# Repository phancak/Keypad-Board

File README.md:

# STM32L010K4T6 Keypad Board  

## Overview  
This project features a **low-power, compact keypad module** based on the **STM32L010K4T6 MCU**, designed to function as a **mini keyboard** for embedded systems. The board includes **twelve tactile buttons**, with the STM32 MCU handling **debouncing and key scanning**, then transmitting keypress data to a host MCU via **I2C or UART**.  

This design optimizes processing efficiency on the host system by **offloading keypad management to the STM32L010K4T6**, making it ideal for applications requiring reliable **user input with minimal power consumption**.  

## Features  
✅ **STM32L010K4T6 MCU** – Ultra-low-power ARM Cortex-M0+ processor  
✅ **12-Button Keypad** – Efficient, responsive user input  
✅ **I2C & UART Communication** – Flexible interfacing with host MCUs  
✅ **Debouncing & Key Scanning** – Handled in firmware for accurate input detection  
✅ **Low Power Mode** – Automatic sleep mode when idle to conserve energy  

## Applications  
- **Embedded Systems** – User interface for microcontroller-based projects  
- **IoT Devices** – Low-power control panel for smart devices  
- **Industrial Automation** – Secure keypad entry for control units  

## Getting Started  
### Hardware Requirements  
- STM32L010K4T6 Keypad Board  
- Host MCU (STM32, ESP32, Raspberry Pi, etc.)  
- Power Supply (3.3V)  
- USB-to-Serial Debugging Tools  

### Software Requirements  
- **STM32CubeIDE** – Firmware development  
- **I2C/UART Libraries** – Communication with the host MCU  
- **ST-Link or J-Link** – Debugging and flashing tools  

## Setup & Usage  
1. **Power the Board** – Provide 3.3V supply to the MCU.  
2. **Connect to Host MCU** – Use I2C or UART for communication.  
3. **Flash Firmware** – Load key scanning and communication code.  
4. **Receive Key Data** – Host MCU processes key events for input handling.  

## Repository Structure  
/Firmware - STM32 firmware source code
/Core - Main application files
/Drivers - HAL and LL peripheral drivers
/Keypad - Debouncing and key scanning logic
/Utils - Utility functions and helper libraries

/Hardware - PCB schematics and design files
/Schematic - Circuit diagrams (PDF, KiCad, Altium, etc.)
/PCB - Board layout files (Gerber, BOM, assembly files)

/Docs - Technical documentation and references
/Getting_Started - Setup guides, connection diagrams
/Datasheets - Component datasheets
/Application_Notes - Project use cases and performance analysis

/Examples - Sample projects demonstrating board usage
/I2C_Host - Example of interfacing via I2C
/UART_Host - Example of interfacing via UART

/Tools - Development tools and scripts
/Flashing_Scripts - Python scripts for automated flashing
/Debug_Scripts - Debugging utilities for logging

## Future Enhancements  
- 🔹 **Configurable Key Mapping** – Customize key assignments via firmware  
- 🔹 **Multi-Press Support** – Enable simultaneous key detection  
- 🔹 **Low-Power Optimization** – Further reduce power consumption for battery-based applications  

## License  
This project is open-source under the **MIT License**.  

---

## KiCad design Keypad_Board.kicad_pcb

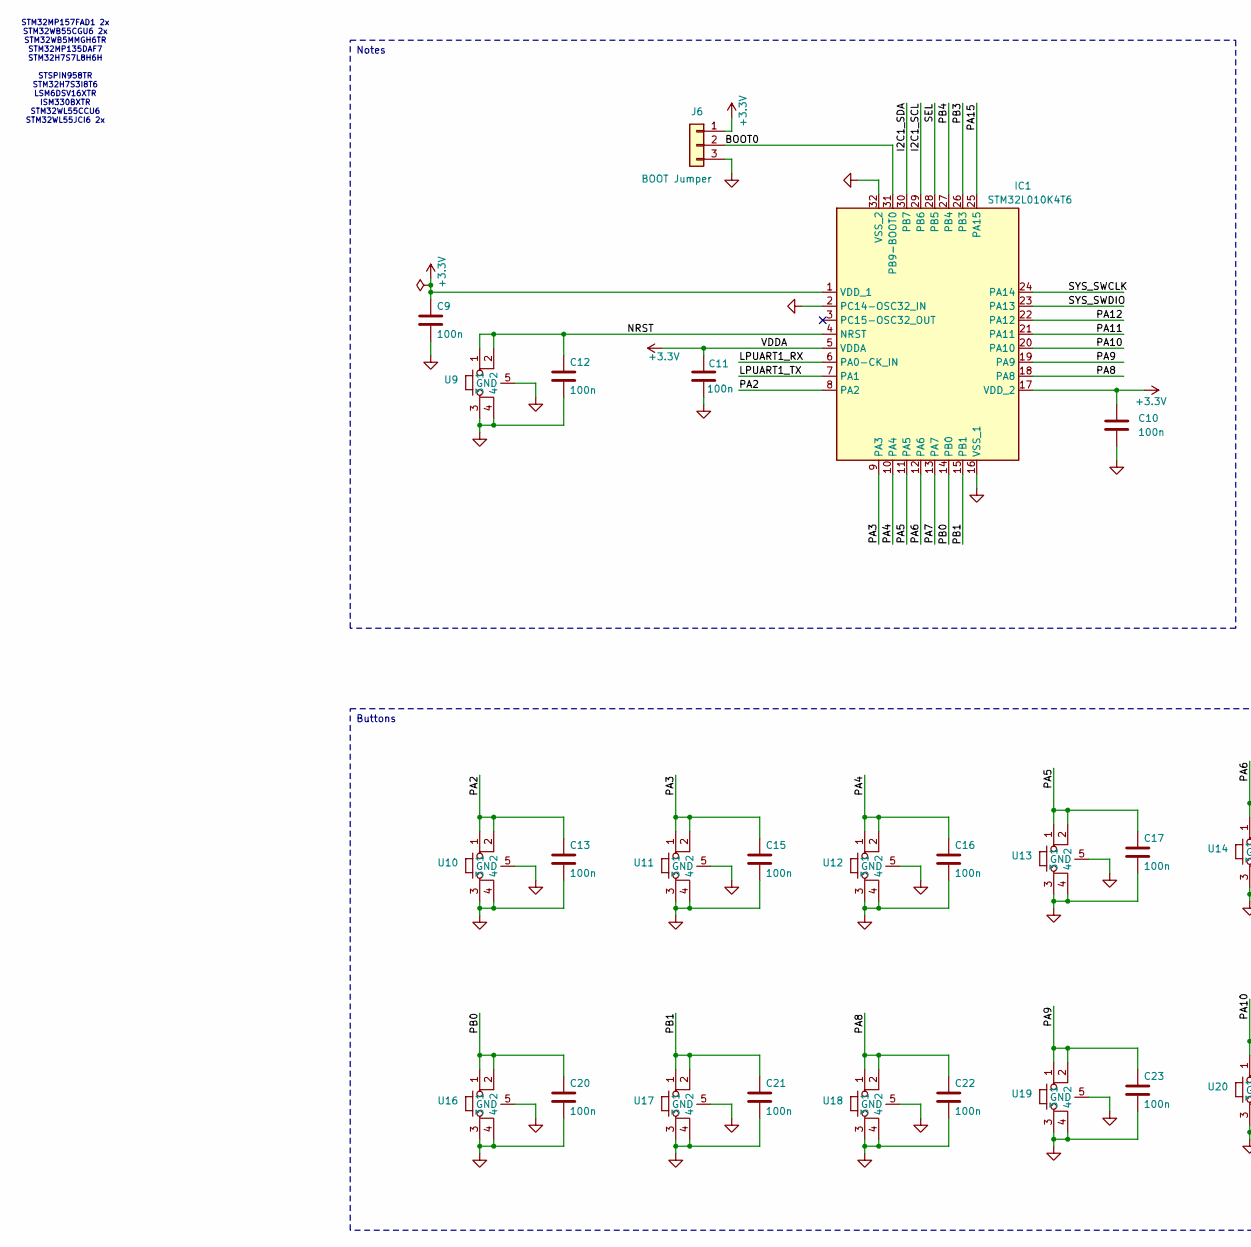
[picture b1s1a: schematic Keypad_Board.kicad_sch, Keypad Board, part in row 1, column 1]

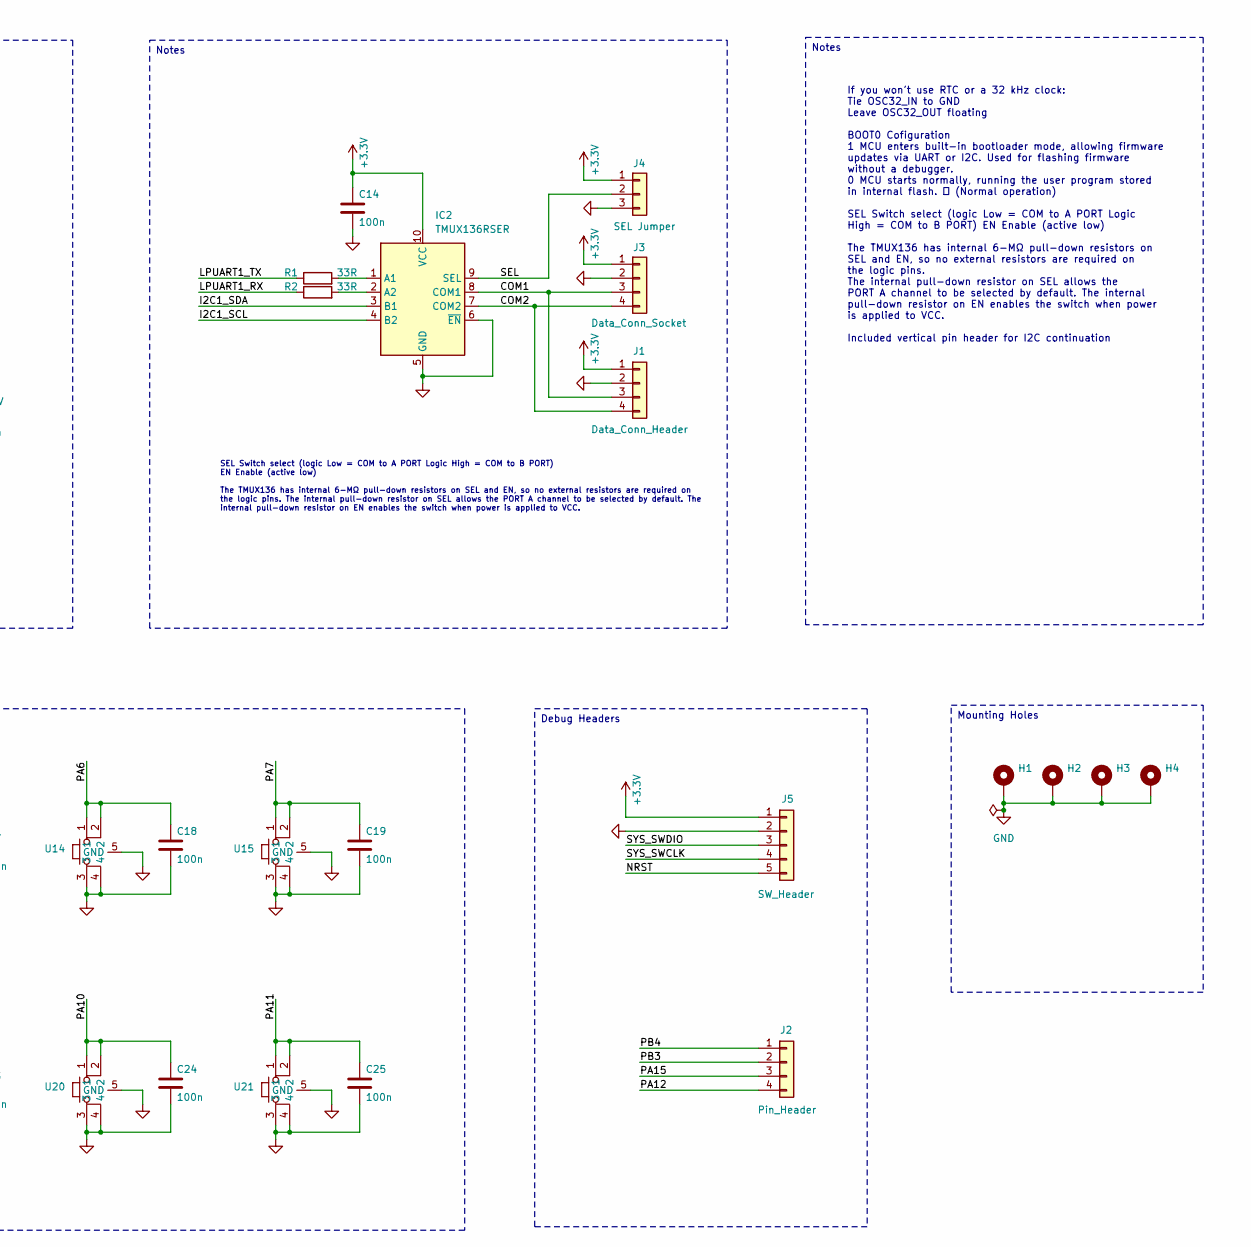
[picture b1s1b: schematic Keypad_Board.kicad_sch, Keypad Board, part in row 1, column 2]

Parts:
C9, C10, C11, C12, C13, C14, C15, C16, C17, C18, C19, C20, C21, C22, C23, C24, C25: 100n; C_0603_1608Metric_Pad1.08x0.95mm_HandSolder
H1, H2, H3, H4: MountingHole_Pad; MountingHole_3.2mm_M3_Pad
IC1: STM32L010K4T6; STM32L010K4T6 _QFP80P900X900X160-32N; Manufacturer_Part_Number STM32L010K4T6; Mouser Part Number 511-STM32L010K4T6
IC2: TMUX136RSER; Mouser Part Number 595-TMUX136RSER
J1: Data_Conn_Header; PinHeader_1x04_P2.54mm_Vertical
J2: Pin_Header; PinHeader_1x04_P2.54mm_Vertical
J3: Data_Conn_Socket; PinSocket_1x04_P2.54mm_Vertical
J4: SEL Jumper; PinHeader_1x03_P2.54mm_Vertical
J5: SW_Header; PinHeader_1x05_P2.54mm_Vertical
J6: BOOT Jumper; PinHeader_1x03_P2.54mm_Vertical
R1, R2: 33R; R_0805_2012Metric_Pad1.20x1.40mm_HandSolder
U9, U10, U11, U12, U13, U14, U15, U16, U17, U18, U19, U20, U21: Button_KMR231GLFS

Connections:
+3.3V: C9.1, C10.1, C11.1, C14.1, IC1.1 (VDD_1), IC1.5 (VDDA), IC1.17 (VDD_2), IC2.10 (VCC), J1.1, J3.1, J4.1, J5.1, J6.1
/BOOT0: IC1.31 (PB9-BOOT0), J6.2
/COM1: IC2.8 (COM1), J1.3, J3.3
/COM2: IC2.7 (COM2), J1.4, J3.4
/I2C1_SCL: IC1.29 (PB6), IC2.4 (B2)
/I2C1_SDA: IC1.30 (PB7), IC2.3 (B1)
/LPUART1_RX: IC1.6 (PA0-CK_IN), R2.1
/LPUART1_TX: IC1.7 (PA1), R1.1
/NRST: C12.1, IC1.4 (NRST), J5.5, U9.1, U9.2
/PA2: C13.1, IC1.8 (PA2), U10.1, U10.2
/PA3: C15.1, IC1.9 (PA3), U11.1, U11.2
/PA4: C16.1, IC1.10 (PA4), U12.1, U12.2
/PA5: C17.1, IC1.11 (PA5), U13.1, U13.2
/PA6: C18.1, IC1.12 (PA6), U14.1, U14.2
/PA7: C19.1, IC1.13 (PA7), U15.1, U15.2
/PA8: C22.1, IC1.18 (PA8), U18.1, U18.2
/PA9: C23.1, IC1.19 (PA9), U19.1, U19.2
/PA10: C24.1, IC1.20 (PA10), U20.1, U20.2
/PA11: C25.1, IC1.21 (PA11), U21.1, U21.2
/PA12: IC1.22 (PA12), J2.4
/PA15: IC1.25 (PA15), J2.3
/PB0: C20.1, IC1.14 (PB0), U16.1, U16.2
/PB1: C21.1, IC1.15 (PB1), U17.1, U17.2
/PB3: IC1.26 (PB3), J2.2
/PB4: IC1.27 (PB4), J2.1
/SEL: IC1.28 (PB5), IC2.9 (SEL), J4.2
/SYS_SWCLK: IC1.24 (PA14), J5.4
/SYS_SWDIO: IC1.23 (PA13), J5.3
GND: C9.2, C10.2, C11.2, C12.2, C13.2, C14.2, C15.2, C16.2, C17.2, C18.2, C19.2, C20.2, C21.2, C22.2, C23.2, C24.2, C25.2, H1.1, H2.1, H3.1, H4.1, IC1.2 (PC14-OSC32_IN), IC1.16 (VSS_1), IC1.32 (VSS_2), IC2.5 (GND), IC2.6 (~EN), J1.2, J3.2, J4.3, J5.2, J6.3, U9.3, U9.4, U9.5 (GND), U10.3, U10.4, U10.5 (GND), U11.3, U11.4, U11.5 (GND), U12.3, U12.4, U12.5 (GND), U13.3, U13.4, U13.5 (GND), U14.3, U14.4, U14.5 (GND), U15.3, U15.4, U15.5 (GND), U16.3, U16.4, U16.5 (GND), U17.3, U17.4, U17.5 (GND), U18.3, U18.4, U18.5 (GND), U19.3, U19.4, U19.5 (GND), U20.3, U20.4, U20.5 (GND), U21.3, U21.4, U21.5 (GND)
unnamed: IC2.1 (A1), R1.2
unnamed: IC2.2 (A2), R2.2

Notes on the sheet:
Notes
Debug Headers
Mounting Holes
Buttons
If you won't use RTC or a 32 kHz clock: Tie OSC32_IN to GND Leave OSC32_OUT floating BOOT0 Cofiguration 1 MCU enters built-in bootloader mode, allowing firmware updates via UART or I2C. Used for flashing firmware without a debugger. 0 MCU starts normally, running the user program stored in internal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
SEL Switch select (logic Low = COM to A PORT Logic High = COM to B PORT) EN Enable (active low) The TMUX136 has internal 6-MΩ pull-down resistors on SEL and EN, so no external resistors are required on the logic pins. The internal pull-down resistor on SEL allows the PORT A channel to be selected b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
STM32MP157FAD1 2x STM32WB55CGU6 2x STM32WB5MMGH6TR STM32MP135DAF7 STM32H7S7L8H6H STSPIN958TR STM32H7S3I8T6 LSM6DSV16XTR ISM330BXTR STM32WL55CCU6 STM32WL55JCI6 2x

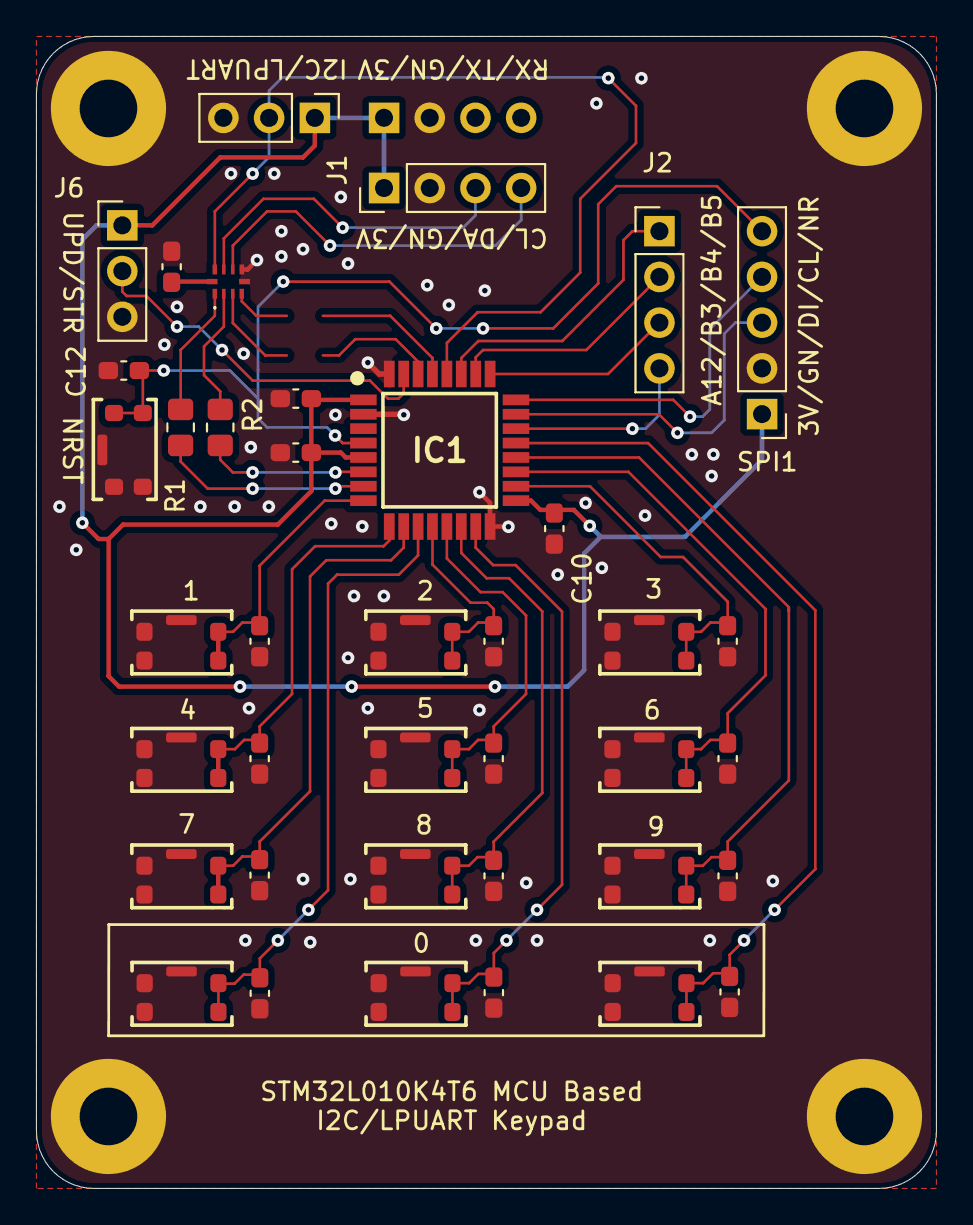
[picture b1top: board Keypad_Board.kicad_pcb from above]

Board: 2 copper layers, 50.0 x 64.0 mm, 44 parts (1 on the bottom side), 31 nets.
